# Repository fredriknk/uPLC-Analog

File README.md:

# μPLC - Analog
### Pcbway Sponsorship
Thanks so much to [PCBWay](https://www.pcbway.com/) who offered to assemble my first prototype batch of all three [uPLC modules](https://github.com/fredriknk/uPLC-stack). They deliver awesome quality as always, see the result for yourself below.

I now have two prototypes of the uPLC-Analog so ESP-Home integrations will come soon.

ESP micro PLC the size of a post stamp. The uPLC-analog version is an [ESP-32-C3](./DOCUMENTATION/esp-12f_product_specification_en.pdf) wifi, bluetooth module for communication and MCU, it has a 3.8-24V buck regulator, has four single ended / two differential 0-3V analog inputs through a [ADS1115](./DOCUMENTATION/ads1115.pdf), one 12 bit 3.6msps analog dac through a [MCP4725A0T](./DOCUMENTATION/Microchip-Tech-MCP4725A0T-E-CH_C144198.pdf) , and one protected 3.3v GPIO for onwire communication (Eg for DS18b20 sensors). The analog uPLC allso has input voltage monitoring for battery applications. 

[Schematic](./DOCUMENTATION/_schematic.pdf)

[Assembly IBOM](https://htmlpreview.github.io/?https://raw.githubusercontent.com/fredriknk/uplc-analog/main/DOCUMENTATION/ibom.html)

## Specifications
| **Parameter**   | **Description**                                                     |
|-----------------|---------------------------------------------------------------------|
| _Input voltage_ | 3.8-24v                               |
| _Current_       | TBD Wifi: ##mA, Radio Off: ##mA, Deep sleep ##uA |  
| _Communication_ | 2.4ghz WIFI, Uart TTL                            |
| _Baudrate_      | 115200                                                              |
| _PCB size_      | 22x31.4mm                                                             |
| _PCB info_      | 1.6mm FR4, HASL lead free, 4 layer               |
| _Case size_     | XxXxXmm TBD                                                         |

## FIRST PRODUCTION PROTOTYPE
TODO

## Connector

| **Label**   | **GPIO**|**Description**       |
|------------|-----|-------------------------|
|_3V3_ | 3V3 | 3.3v output for sensor connection |
|_ONE-W_ | GPIO18  | Protected gpio for onewire comm |
|_GND_ | GND | GND port for sensor connection|
|_GND_ | GND | GND port for sensor connection |
|_3V0_ | 3V0 | 3.0v rail for analog input connections |
|_AOUT0_ | DAC  | i2c DAC 0-3v3 analog Output  |
|_AIN0_ | ADC1  | i2c ADC 0-3v0 analog input  |
|_AIN1_ | ADC2  | i2c ADC 0-3v0 analog input  |
|_AIN2_ | ADC3  | i2c ADC 0-3v0 analog input  |
|_AIN3_ | ADC4  | i2c ADC 0-3v0 analog input  |
|_GND_ | GND |  Ground  |
|_4-24V_ | Buck reg |3.8-24v polarity protected power input |

## PCB Pictures
Pcb-assembly by [PCBWay](https://www.pcbway.com/)

## Homeassistant Implementation
TODO

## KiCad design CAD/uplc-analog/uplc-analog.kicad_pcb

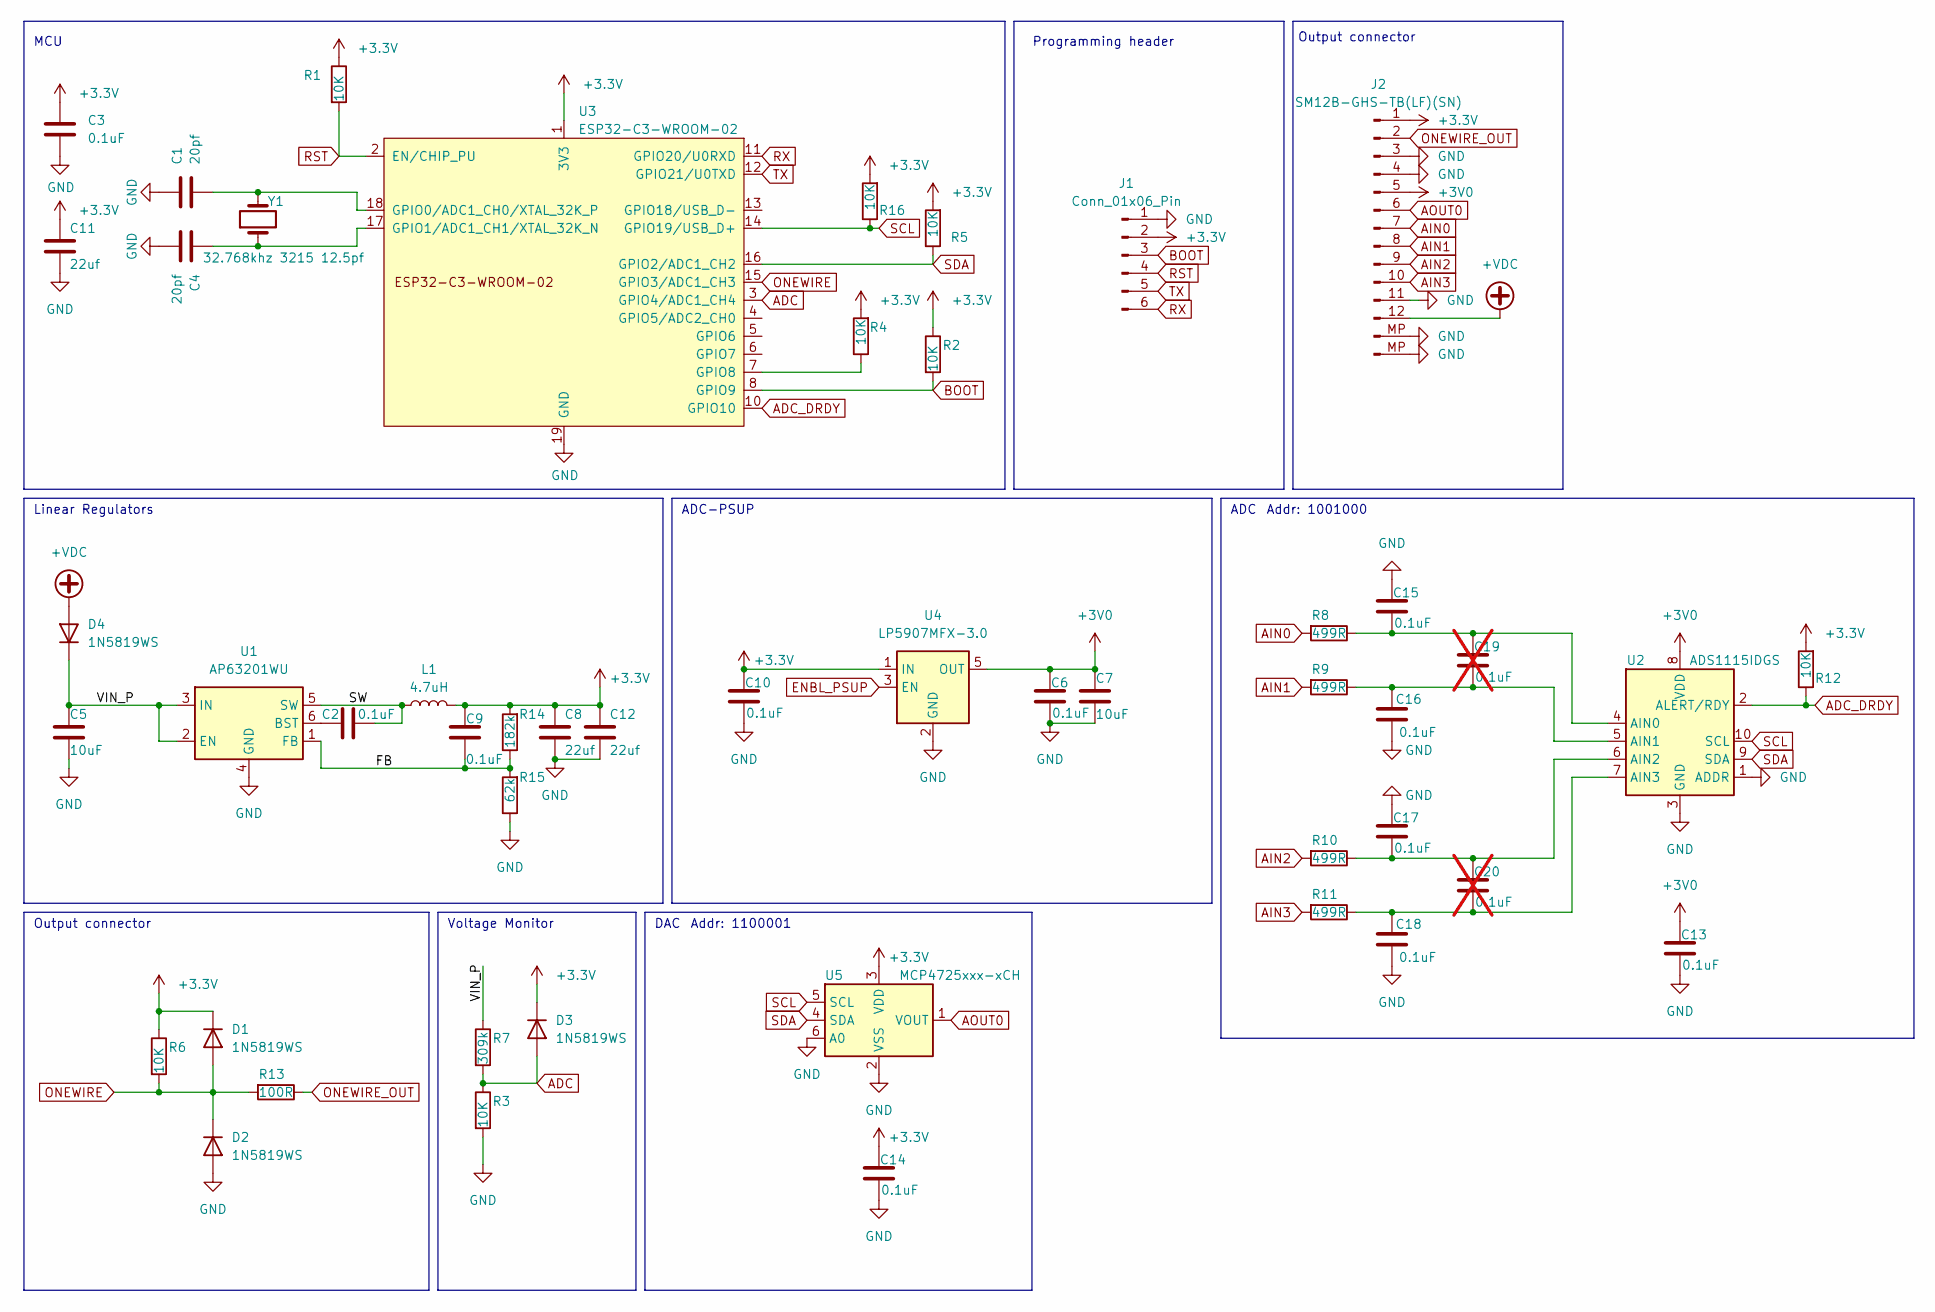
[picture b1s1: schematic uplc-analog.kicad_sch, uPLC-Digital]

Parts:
C1, C4: 20pf; C_0402_1005Metric; MPN 0402CG200J500NT; LCSC Part # C1554
C2, C3, C6, C9, C10, C13, C14, C15, C16, C17, C18: 0.1uF; C_0402_1005Metric; MPN GRM155R71H104KE14D; LCSC Part # C77020
C5, C7: 10uF; C_0805_2012Metric; MPN GRM21BR6YA106KE43L; LCSC Part # C162422
C8, C11, C12: 22uf; C_0402_1005Metric; MPN GRM155R60J226ME11D; LCSC Part # C415703
C19, C20: 0.1uF; C_0402_1005Metric; MPN GRM155R71H104KE14D; LCSC Part # C77020; not fitted
D1, D2, D3, D4: 1N5819WS; D_SOD-323; MPN 1N5819WS; LCSC Part # C191023
J1: Conn_01x06_Pin; TestPoint_Pad_1.0x1.0mm_6pad; LCSC Part # DNP
J2: SM12B-GHS-TB(LF)(SN); JST_GH_SM12B-GHS-TB_1x12-1MP_P1.25mm_Horizontal; MPN SM12B-GHS-TB(LF)(SN); LCSC Part # C265421
L1: 4.7uH; L_1008_2520Metric; MPN LQM2HPN4R7MG0L; LCSC Part # C82314
R1, R2, R3, R4, R5, R6, R12, R16: 10K; R_0402_1005Metric; MPN 0402WGF1002TCE; LCSC Part # C25744
R7: 309k; R_0402_1005Metric; MPN RTT023093FTH; LCSC Part # C159040
R8, R9, R10, R11: 499R; R_0402_1005Metric; MPN 0402WGF4990TCE; LCSC Part # C4125
R13: 100R; R_0402_1005Metric; MPN 0402WGF1000TCE; LCSC Part # C25076
R14: 182k; R_0402_1005Metric; MPN 0402WGF1823TCE; LCSC Part # C11481
R15: 62k; R_0402_1005Metric; MPN RC0402FR-0762KL; LCSC Part # C137950
U1: AP63201WU; TSOT-23-6; MPN AP63201WU-7; LCSC Part # C2071044
U2: ADS1115IDGS; TSSOP-10_3x3mm_P0.5mm; MPN ADS1115IDGSR; LCSC Part # C37593
U3: ESP32-C3-WROOM-02; MPN ESP32-C3-WROOM-02-N4; LCSC Part # C2934560
U4: LP5907MFX-3.0; SOT-23-5; MPN LP5907MFX-3.0/NOPB; LCSC Part # C475492
U5: MCP4725xxx-xCH; SOT-23-6; MPN MCP4725A0T-E/CH; LCSC Part # C144198
Y1: 32.768khz 3215 12.5pf; Crystal_SMD_3215-2Pin_3.2x1.5mm; MPN Q13FC13500004; LCSC Part # C32346

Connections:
+3.3V: C3.1, C8.1, C9.1, C10.1, C11.1, C12.1, C14.1, D1.1 (K), D3.1 (K), J1.2, J2.1, L1.2, R1.1, R2.1, R4.2, R5.2, R6.1, R12.2, R14.2, R16.2, U3.1 (3V3), U4.1 (IN), U5.3 (VDD)
+3V0: C6.1, C7.1, C13.1, J2.5, U2.8 (VDD), U4.5 (OUT)
+VDC: D4.2 (A), J2.12
/FB: C9.2, R14.1, R15.2, U1.1 (FB)
/SW: C2.1, L1.1, U1.5 (SW)
/VIN_P: C5.1, D4.1 (K), R7.1, U1.2 (EN), U1.3 (IN)
ADC: D3.2 (A), R3.1, R7.2, U3.3 (GPIO4/ADC1_CH4)
ADC_DRDY: R12.1, U2.2 (ALERT/RDY), U3.10 (GPIO10)
AIN0: J2.7, R8.2
AIN1: J2.8, R9.2
AIN2: J2.9, R10.2
AIN3: J2.10, R11.2
AOUT0: J2.6, U5.1 (VOUT)
BOOT: J1.3, R2.2, U3.8 (GPIO9)
ENBL_PSUP: U4.3 (EN)
GND: C1.1, C3.2, C4.2, C5.2, C6.2, C7.2, C8.2, C10.2, C11.2, C12.2, C13.2, C14.2, C15.1, C16.1, C17.1, C18.1, D2.2 (A), J1.1, J2.3, J2.4, J2.11, J2.MP (Pin_13), R3.2, R15.1, U1.4 (GND), U2.1 (ADDR), U2.3 (GND), U3.9 (GND), U3.19 (GND), U4.2 (GND), U5.2 (VSS), U5.6 (A0)
unnamed: C2.2, U1.6 (BST)
unnamed: C15.2, C19.1, R8.1, U2.4 (AIN0)
unnamed: C16.2, C19.2, R9.1, U2.5 (AIN1)
unnamed: C17.2, C20.1, R10.1, U2.6 (AIN2)
unnamed: C18.2, C20.2, R11.1, U2.7 (AIN3)
unnamed: C1.2, U3.18 (GPIO0/ADC1_CH0/XTAL_32K_P), Y1.2
unnamed: C4.1, U3.17 (GPIO1/ADC1_CH1/XTAL_32K_N), Y1.1
unnamed: R4.1, U3.7 (GPIO8)
ONEWIRE: D1.2 (A), D2.1 (K), R6.2, R13.2, U3.15 (GPIO3/ADC1_CH3)
ONEWIRE_OUT: J2.2, R13.1
RST: J1.4, R1.2, U3.2 (EN/CHIP_PU)
RX: J1.6, U3.11 (GPIO20/U0RXD)
SCL: R16.1, U2.10 (SCL), U3.14 (GPIO19/USB_D+), U5.5 (SCL)
SDA: R5.1, U2.9 (SDA), U3.16 (GPIO2/ADC1_CH2), U5.4 (SDA)
TX: J1.5, U3.12 (GPIO21/U0TXD)

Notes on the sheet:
ADC
Linear Regulators
MCU
Output connector
Addr: 1001000
Programming header
DAC
Addr: 1100001
Voltage Monitor
ADC-PSUP

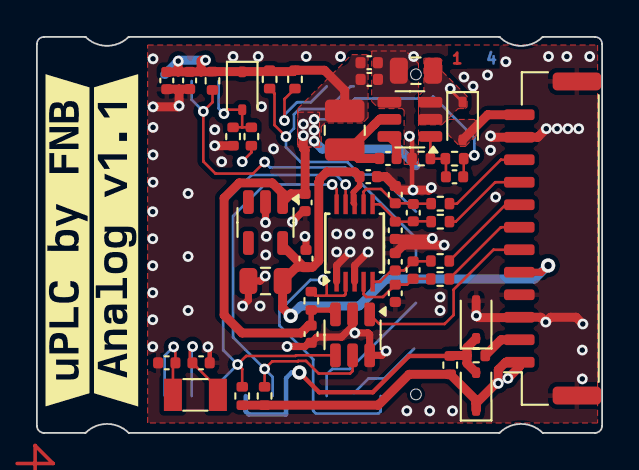
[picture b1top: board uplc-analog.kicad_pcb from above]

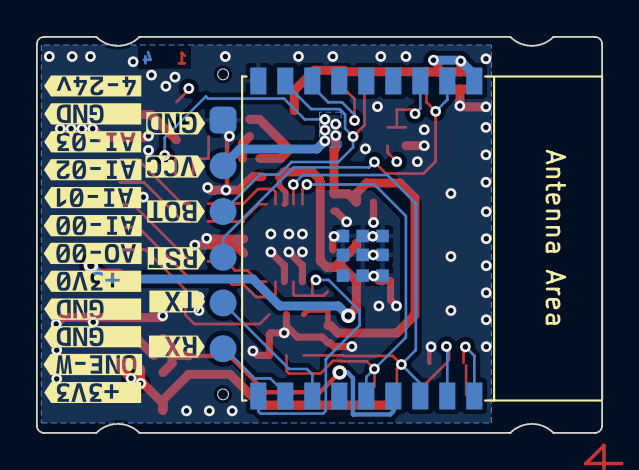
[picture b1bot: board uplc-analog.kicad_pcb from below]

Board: 4 copper layers, 31.4 x 22.0 mm, 69 parts (20 on the bottom side), 30 nets.

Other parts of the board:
kibuzzard-65D74DE1, kibuzzard-65D74DE1#2: G***; kibuzzard-65D74DE1
kibuzzard-65D74DEE: G***; kibuzzard-65D74DEE
kibuzzard-65D74DFB: G***; kibuzzard-65D74DFB
kibuzzard-65D460A0: G***; kibuzzard-65D460A0
kibuzzard-65D3616E: G***; kibuzzard-65D3616E
kibuzzard-65D7176D: G***; kibuzzard-65D7176D
kibuzzard-65D7177B: G***; kibuzzard-65D7177B
kibuzzard-65D36177: G***; kibuzzard-65D36177
kibuzzard-65D46022: G***; kibuzzard-65D46022
kibuzzard-65D46066: G***; kibuzzard-65D46066
kibuzzard-65D49092: G***; kibuzzard-65D49092
kibuzzard-65D71774: G***; kibuzzard-65D71774
kibuzzard-65DC95DA: G***; kibuzzard-65DC95DA
kibuzzard-65DC95E5: G***; kibuzzard-65DC95E5
kibuzzard-65DC95EF: G***; kibuzzard-65DC95EF
kibuzzard-65DC95F6: G***; kibuzzard-65DC95F6
kibuzzard-65DC961D: G***; kibuzzard-65DC961D
kibuzzard-65DC9610: G***; kibuzzard-65DC9610
kibuzzard-65DCE4DE: G***; kibuzzard-65DCE4DE

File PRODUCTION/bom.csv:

Designator,Footprint,Quantity,Value,LCSC Part #
"C1, C4",0402,2,20pf,C1554
"C10, C13, C14, C15, C16, C17, C18, C2, C3, C6, C9",0402,11,0.1uF,C307331
"C11, C12, C8",0402,3,22uf,C415703
"C19, C20",0402,2,1uF,DNP
"C5, C7",0805,2,10uF,C162422
"D1, D2, D3, D4",D_SOD-323,4,1N5819WS,C191023
J1,TestPoint_Pad_1.0x1.0mm_6pad,1,Conn_01x06_Pin,DNP
J2,JST_GH_SM12B-GHS-TB_1x12-1MP_P1.25mm_Horizontal,1,SM12B-GHS-TB(LF)(SN),C265421
L1,1008,1,6.8uH,C98340
"R1, R12, R16, R2, R3, R4, R5, R6",0402,8,10K,C25744
"R10, R11, R8, R9",0402,4,499R,C25076
R13,0402,1,100R,C25076
R14,0402,1,182k,C11481
R15,0402,1,62k,C137950
R7,0402,1,309k,
U1,TSOT-23-6,1,AP63201WU,C2071044
U2,TSSOP-10_3x3mm_P0.5mm,1,ADS1115IDGS,
U3,ESP32-C3-WROOM-02,1,ESP32-C3-WROOM-02,C2934560
U4,SOT-23-5,1,LP5907MFX-3.0,
U5,SOT-23-6,1,MCP4725xxx-xCH,
Y1,Crystal_SMD_3215-2Pin_3.2x1.5mm,1,32.768khz 3215 12.5pf,C32346

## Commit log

2024-02-26 first commit v1.1
2024-02-27 Rev 1.1
2024-10-14 Panelization changes
2024-10-14 Updated readme and documentation to analog
2025-04-09 Feat: Production update
